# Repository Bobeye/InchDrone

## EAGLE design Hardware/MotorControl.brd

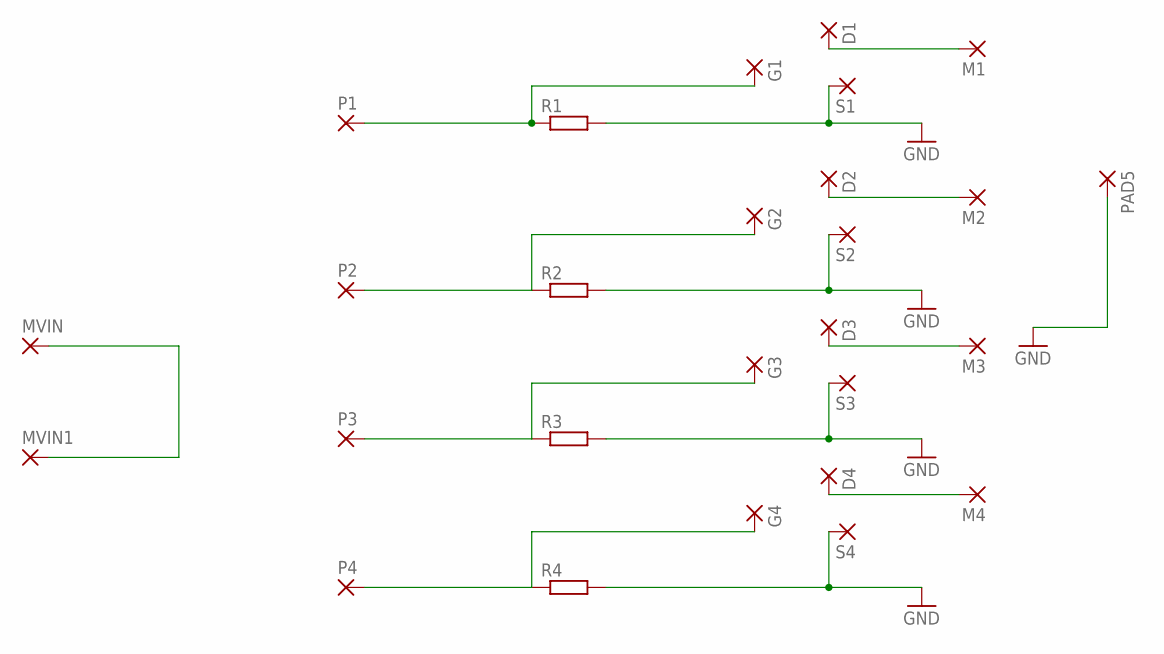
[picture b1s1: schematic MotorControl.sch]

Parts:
D1, D2, D3, D4: 1,6/0,8
G1, G2, G3, G4: 1,6/0,8
M1, M2, M3, M4: 2,15/1,0
MVIN, MVIN1: 2,15/1,0
P1, P2, P3, P4: 2,15/1,0
PAD5: 2,15/1,0
R1, R2, R3, R4: R0207/10; 0207/10
S1, S2, S3, S4: 1,6/0,8

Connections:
GND: PAD5.1, R1.2, R2.2, R3.2, R4.2, S1.1, S2.1, S3.1, S4.1
unnamed: G1.1, P1.1, R1.1
unnamed: D1.1, M1.1
unnamed: G2.1, P2.1, R2.1
unnamed: D3.1, M3.1
unnamed: G3.1, P3.1, R3.1
unnamed: D4.1, M4.1
unnamed: G4.1, P4.1, R4.1
unnamed: D2.1, M2.1
unnamed: MVIN.1, MVIN1.1

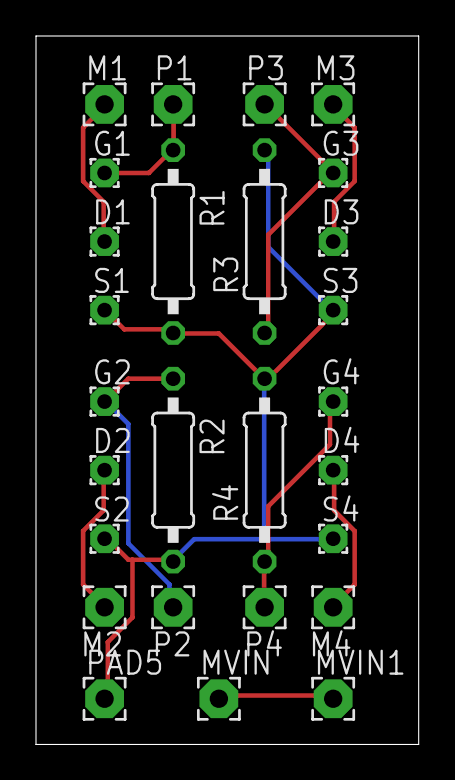
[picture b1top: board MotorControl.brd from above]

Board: 2 copper layers, 21.3 x 39.4 mm, 27 parts (0 on the bottom side), 10 nets.

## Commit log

2016-04-17 Inch Drone repositoty

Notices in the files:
parts and their libraries:
SparkFun-Aesthetics: Licensing: Creative Commons ShareAlike 4.0 International - https://creativecommons.org/licenses/by-sa/4.0
